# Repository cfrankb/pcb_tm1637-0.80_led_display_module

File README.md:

# TM1637 7-Segments 0.80" LED Module

## Introduction

This is a pcb design for the 0.80" LED 7-Segments Display Module. The board is pin compatible with the standard 0.56" LED 7-Segments Display Module

This hardware module is supported by a native C++ driver implementation (linked below), demonstrating a full-stack IoT approach from physical PCB to firmware abstraction.

Reflowed using a controlled hotplate process with lead-free solder paste (SAC305). The screen was hand soldered using a standard soldering iron. The screen can be attached directly or socketed.

## Features

 * Display numbers
 * Display raw segment data
 * Scrolling text
 * Simplified interface
 * C++ Implementation

ESP32 driver for this board [GitHub cfrankb/esp32-tm1637plus-cpp](https://github.com/cfrankb/esp32-tm1637plus-cpp).

## 0.80" 7-Segments LED Displays Tested

| Part #    | Size  | Pins |
| --------- | ----- | ---- |
| 8041BS-1  | 0.80" | 12   |
| 8401BS-1F | 0.80" | 14*  |

\* Requires a 2.54mm female socket.

## Part List

|     | Part #            | REF#   | Package   |
| --- | ----------------- | ------ | --------- |
| 2x  | 100p C            | C1, C2 | 1206      |
| 1x  | 1k Resistor       | R1     | 1206      |
| 2x  | 10k Resistor      | R2, R3 | 1206      |
| 1x  | Green Led         | D1     | 0805      |
| 1x  | 1u C              | C3     | 1206      |
| 1x  | 100u Tantalum C   | C4     | 3216      |
| 1x  | TM1637            | U1     | SOP-20    |
| 1x  | 0.80" LED Display | U2     | see above |

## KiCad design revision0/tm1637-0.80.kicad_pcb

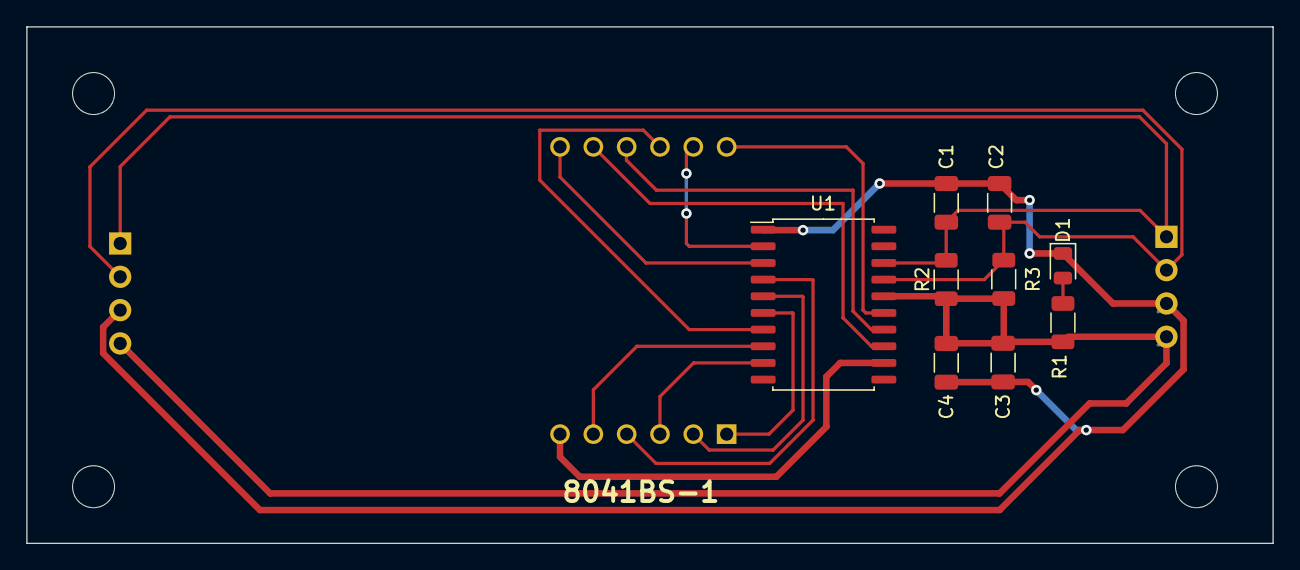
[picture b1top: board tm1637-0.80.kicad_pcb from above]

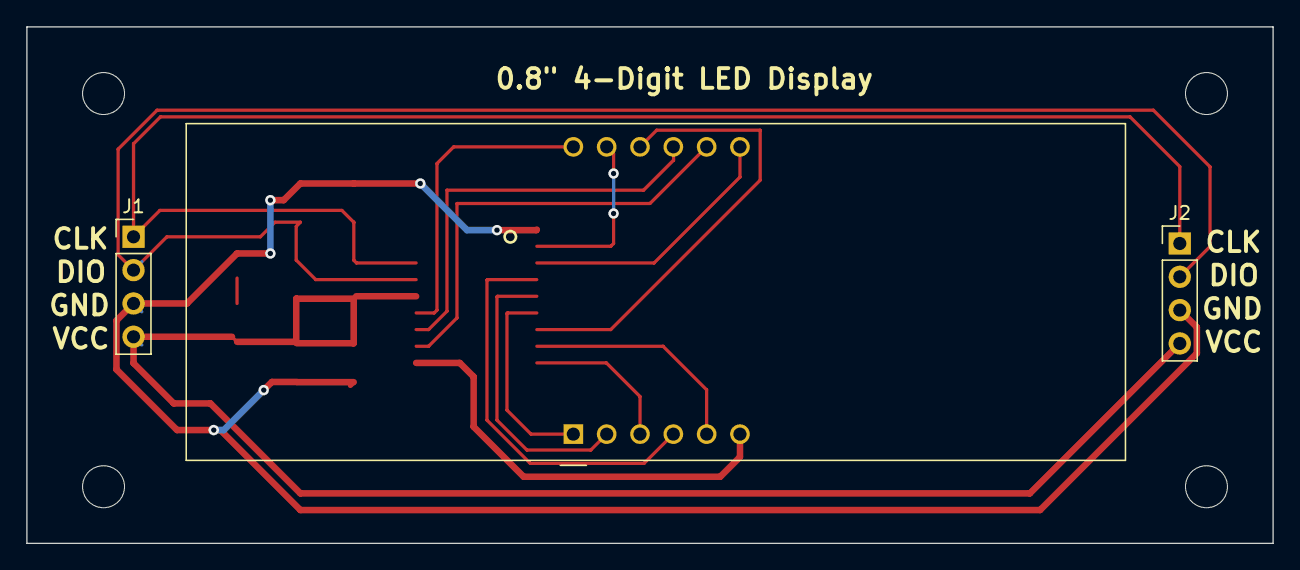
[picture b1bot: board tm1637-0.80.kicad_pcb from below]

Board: 2 copper layers, 95.0 x 39.4 mm, 16 parts (7 on the bottom side), 17 nets.

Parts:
C1, C2: 100p; C_1206_3216Metric
C3: 1u; C_1206_3216Metric
C4: 100u; C_1206_3216Metric
D1: LED; LED_0805_2012Metric
H1, H2, H3, H4: MountingHole; MountingHole_3.2mm_M3
J1, J2: Conn_01x04; PinHeader_1x04_P2.54mm_Vertical
R1: 1k; R_1206_3216Metric
R2, R3: 10k; R_1206_3216Metric
U1: TM1637; SOP-20_7.5x12.8mm_P1.27mm
U2: CA56-12SRWA; 8041AS

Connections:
GNDREF: C1.2, C2.2, C3.2, C4.2, D1.1 (K), J1.3, J2.3, U1.1 (GND)
unnamed: D1.2 (A), R1.2
unnamed: C1.1, J1.1, J2.1, R2.2, U1.18 (CLK)
unnamed: C2.1, J1.2, J2.2, R3.2, U1.17 (DIO)
unnamed: U1.15 (GRID1), U2.12 (CA1)
unnamed: U1.14 (GRID2), U2.9 (CA2)
unnamed: U1.13 (GRID3), U2.8 (CA3)
unnamed: U1.12 (GRID4), U2.6 (CA4)
unnamed: U1.2 (SEG1/KS1), U2.11 (a)
unnamed: U1.3 (SEG2/KS2), U2.7 (b)
unnamed: U1.4 (SEG3/KS3), U2.4 (c)
unnamed: U1.5 (SEG4/KS4), U2.2 (d)
unnamed: U1.6 (SEG5/KS5), U2.1 (e)
unnamed: U1.7 (SEG6/KS6), U2.10 (f)
unnamed: U1.8 (SEG7/KS7), U2.5 (g)
unnamed: U1.9 (SEG8/KS8), U2.3 (DPX)
VCC: C3.1, C4.1, J1.4, J2.4, R1.1, R2.1, R3.1, U1.16 (VDD)

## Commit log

2024-09-15 fixed README
2026-03-05 added schematic
2026-03-05 added more details
